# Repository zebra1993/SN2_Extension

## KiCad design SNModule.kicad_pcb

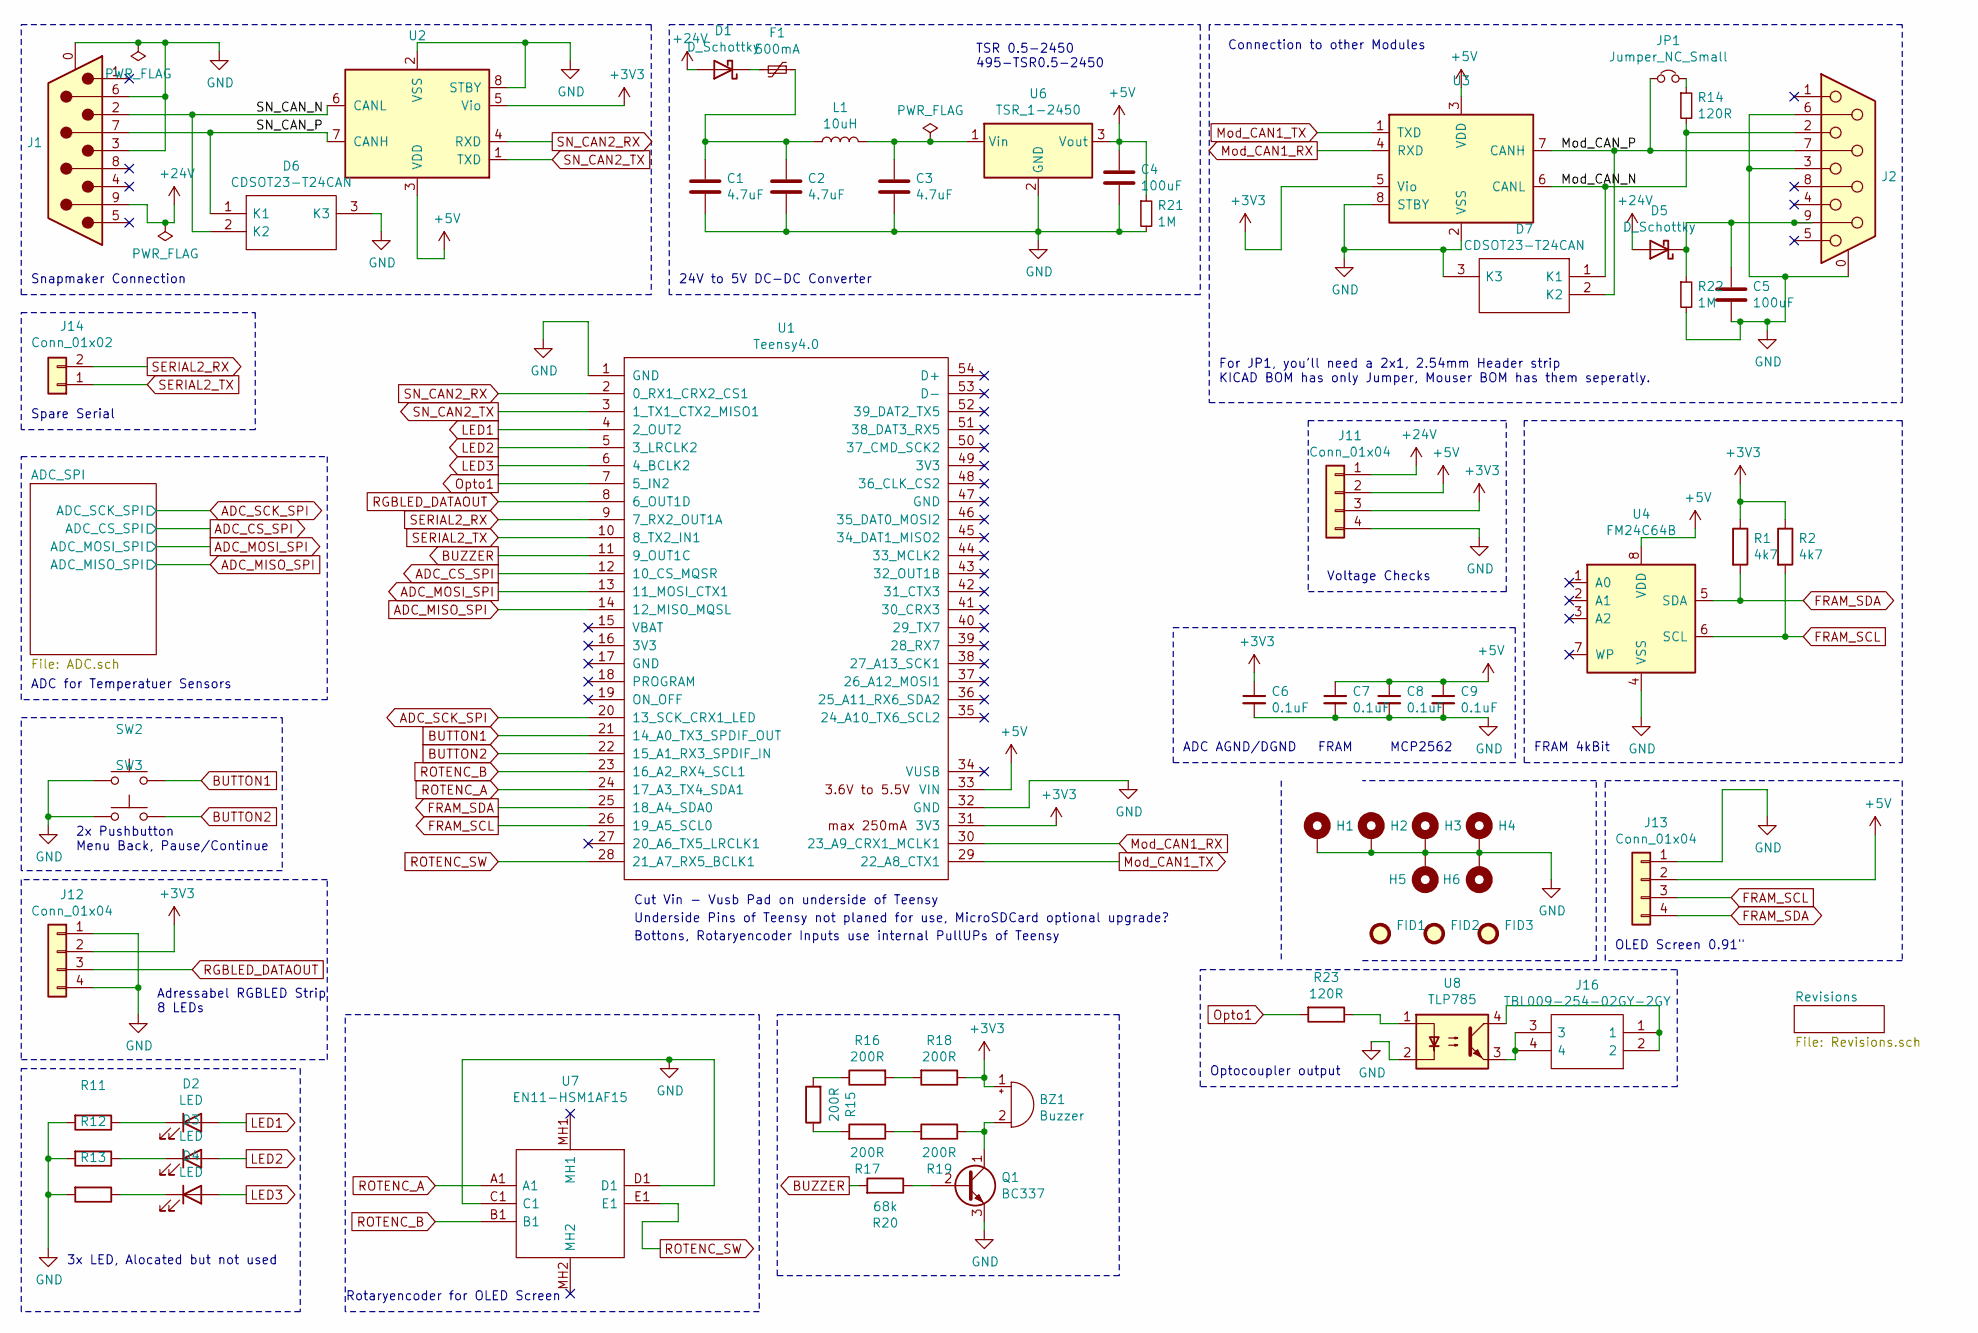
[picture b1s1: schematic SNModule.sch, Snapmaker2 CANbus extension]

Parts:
BZ1: Buzzer; Buzzer_TDK_12.2x6.5RM5; Manufacturer_Part_Number PS1240P02BT; Mouser Part Number 810-PS1240P02BT
C1, C2, C3: 4.7uF; C_1206_HandSoldering; Manufacturer_Part_Number C1206C475K5PACTU; Mouser Part Number 80-C1206C475K5P
C4, C5: 100uF; CP_Elec_6.3x7.7; Manufacturer_Part_Number EEE-FTH101XAL; Mouser Part Number 667-EEE-FTH101XAL
C6, C7, C8, C9: 0.1uF; C_1206_HandSoldering; Manufacturer_Part_Number VJ1206Y104KXXAC; Mouser Part Number 77-VJ1206Y104KXXAC
D1: D_Schottky; D_1206; Manufacturer_Part_Number SD1206T040S1R0; Mouser Part Number 581-SD1206T040S1R0
D2, D3, D4: LED; LED_D5.0mm_FlatTop; Manufacturer_Part_Number LTL-307GE; Mouser Part Number 859-LTL-307GE
D5: D_Schottky; D_2114; Manufacturer_Part_Number SD2114S040S8R0; Mouser Part Number 581-SD2114S040S8R0
D6, D7: CDSOT23-T24CAN; SOT-23; Mouser Part Number 652-CDSOT23-T24CAN
F1: 500mA; Fuse_SMD1206_HandSoldering; Manufacturer_Part_Number 0ZCJ0025AF2E; Mouser Part Number 530-0ZCJ0025AF2E
FID1, FID2, FID3: Fiducial; Fiducial_0.5mm_Dia_1mm_Outer
H1, H2, H3, H4, H5, H6: MountingHole_Pad; MountingHole_4.3mm_M4_Pad_Via
J1: DB9_Male_MountingHoles; D09P23A4GV00LF; Manufacturer_Part_Number D09P23A4GV00LF; Mouser Part Number 649-D09P23A4GV00LF
J2: DB9_Female_MountingHoles; D09S23A4GV00LF; Manufacturer_Part_Number D09S23A4GV00LF; Mouser Part Number 649-D09S23A4GV00LF
J11, J12, J13: Conn_01x04; Socket_Strip_Straight_1x04_Pitch2.54mm; Manufacturer_Part_Number SLW-104-01-T-S; Mouser Part Number 200-SLW10401TS
J14: Conn_01x02; Pin_Header_Straight_1x02_Pitch2.54mm; Manufacturer_Part_Number SLW-102-01-T-S; Mouser Part Number 200-SLW10201TS
J16: TBL009-254-02GY-2GY; TBL00925402GY2GY; Mouser Part Number 490-TBL00925402GY2GY
JP1: Jumper_NC_Small; Pin_Header_Straight_1x02_Pitch2.54mm; Manufacturer_Part_Number SX1100-B; Mouser Part Number 806-SX1100-B
L1: 10uH; L_TracoPower_TCK-047_5.2x5.8mm; Manufacturer_Part_Number TCK-047; Mouser Part Number 495-TCK-047
Q1: BC337; TO-92_Inline_Wide; Manufacturer_Part_Number BC33716TFR; Mouser Part Number 512-BC33716TFR
R1, R2: 4k7; R_1206_HandSoldering; Manufacturer_Part_Number CRCW12064K70FKEA; Mouser Part Number 71-CRCW1206-4.7K-E3
R11, R12, R13, R15, R16, R17, R18, R19: 200R; R_1206_HandSoldering; Manufacturer_Part_Number CRCW1206200RFKEA; Mouser Part Number 71-CRCW1206-200-E3
R14, R23: 120R; R_1206_HandSoldering; Manufacturer_Part_Number CRCW1206120RFKEAC; Mouser Part Number 71-CRCW1206120RFKEAC
R20: 68k; R_1206_HandSoldering; Manufacturer_Part_Number CRCW120668K0FKEA; Mouser Part Number 71-CRCW1206-68K-E3
R21, R22: 1M; R_1206_HandSoldering; Manufacturer_Part_Number CRCW12061M00FKEAC; Mouser Part Number 71-CRCW12061M00FKEAC
SW2, SW3: SW_Push; SW_PUSH_6mm_h4.3mm; Manufacturer_Part_Number ADTS61KV; Mouser Part Number 642-ADTS61KV
U1: Teensy4.0; Teensy40_THT; Manufacturer_Part_Number 4323; Mouser Part Number 485-4323
U2, U3: MCP2562-E-P; DIP-8_W7.62mm_Socket; Manufacturer_Part_Number MCP2562-E/P; Mouser Part Number 579-MCP2562-E/P
U4: FM24C64B; SOIC-8_3.9x4.9mm_Pitch1.27mm; Manufacturer_Part_Number FM24C64B-G; Mouser Part Number 877-FM24C64B-G
U6: TSR_1-2450; DCDC-Conv_TRACO_TSR-1; Manufacturer_Part_Number TSR0.5-2450; Mouser Part Number 495-TSR0.5-2450
U7: EN11-HSM1AF15; EN11HSM1AF15; Mouser Part Number 858-EN11-HSM1AF15
U8: TLP785; DIP-4_W7.62mm_LongPads; Manufacturer_Part_Number TLP785(D4-GR,F; Mouser Part Number 757-TLP785D4-GRF

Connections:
+3V3: BZ1.1 (-), C6.1, J11.3, J12.2, R1.1, R2.1, R18.1, U1.31 (3V3), U2.5 (Vio), U3.5 (Vio); also elsewhere on the board
+5V: C4.1, C7.1, C8.1, C9.1, J11.2, J13.2, R21.1, U1.33 (VIN), U2.3 (VDD), U3.3 (VDD), U4.8 (VDD), U6.3 (Vout)
+24V: D1.2 (A), D5.2 (A), J1.9, J11.1
/Mod_CAN_N: D7.1 (K1), J2.2, R14.2, U3.6 (CANL)
/Mod_CAN_P: D7.2 (K2), J2.7, JP1.1, U3.7 (CANH)
/SN_CAN_N: D6.2 (K2), J1.2, U2.6 (CANL)
/SN_CAN_P: D6.1 (K1), J1.7, U2.7 (CANH)
ADC_CS_SPI: U1.12 (10_CS_MQSR); also elsewhere on the board
ADC_MISO_SPI: U1.14 (12_MISO_MQSL); also elsewhere on the board
ADC_MOSI_SPI: U1.13 (11_MOSI_CTX1); also elsewhere on the board
ADC_SCK_SPI: U1.20 (13_SCK_CRX1_LED); also elsewhere on the board
BUTTON1: SW2.2, U1.21 (14_A0_TX3_SPDIF_OUT)
BUTTON2: SW3.2, U1.22 (15_A1_RX3_SPDIF_IN)
BUZZER: R20.2, U1.11 (9_OUT1C)
FRAM_SCL: J13.3, R2.2, U1.26 (19_A5_SCL0), U4.6 (SCL)
FRAM_SDA: J13.4, R1.2, U1.25 (18_A4_SDA0), U4.5 (SDA)
GND: C1.2, C2.2, C3.2, C4.2, C5.2, C6.2, C7.2, C8.2, C9.2, D6.3 (K3), D7.3 (K3), H1.1, H2.1, H3.1, H4.1, H5.1, H6.1, J1.0 (PAD), J1.3, J1.6, J2.0 (PAD), J2.3, J2.6, J11.4, J12.1, J12.4, J13.1, Q1.3 (E), R11.2, R12.2, R13.2, R21.2, R22.2, SW2.1, SW3.1, U1.1 (GND), U1.32 (GND), U2.2 (VSS), U2.8 (STBY), U3.2 (VSS), U3.8 (STBY), U4.4 (VSS), U6.2 (GND), U7.C1, U7.D1, U8.2; also elsewhere on the board
LED1: D2.2 (A), U1.4 (2_OUT2)
LED2: D3.2 (A), U1.5 (3_LRCLK2)
LED3: D4.2 (A), U1.6 (4_BCLK2)
Mod_CAN1_RX: U1.30 (23_A9_CRX1_MCLK1), U3.4 (RXD)
Mod_CAN1_TX: U1.29 (22_A8_CTX1), U3.1 (TXD)
unnamed: BZ1.2 (+), Q1.1 (C), R19.1
unnamed: C1.1, C2.1, F1.1, L1.1
unnamed: C3.1, L1.2, U6.1 (Vin)
unnamed: C5.1, D5.1 (K), J2.9, R22.1
unnamed: D1.1 (K), F1.2
unnamed: D2.1 (K), R11.1
unnamed: D3.1 (K), R12.1
unnamed: D4.1 (K), R13.1
unnamed: J16.1, J16.2, U8.4
unnamed: J16.3, J16.4, U8.3
unnamed: JP1.2, R14.1
unnamed: Q1.2 (B), R20.1
unnamed: R15.1, R17.2
unnamed: R15.2, R16.1
unnamed: R16.2, R18.2
unnamed: R17.1, R19.2
unnamed: R23.1, U8.1
Opto1: R23.2, U1.7 (5_IN2)
RGBLED_DATAOUT: J12.3, U1.8 (6_OUT1D)
ROTENC_A: U1.24 (17_A3_TX4_SDA1), U7.A1
ROTENC_B: U1.23 (16_A2_RX4_SCL1), U7.B1
ROTENC_SW: U1.28 (21_A7_RX5_BCLK1), U7.E1
SERIAL2_RX: J14.2, U1.9 (7_RX2_OUT1A)
SERIAL2_TX: J14.1, U1.10 (8_TX2_IN1)
SN_CAN2_RX: U1.2 (0_RX1_CRX2_CS1), U2.4 (RXD)
SN_CAN2_TX: U1.3 (1_TX1_CTX2_MISO1), U2.1 (TXD)

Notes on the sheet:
Cut Vin - Vusb Pad on underside of Teensy
Underside Pins of Teensy not planed for use, MicroSDCard optional upgrade?
24V to 5V DC-DC Converter
Snapmaker Connection
Adressabel RGBLED Strip 8 LEDs
ADC for Temperatuer Sensors
Spare Serial
Rotaryencoder for OLED Screen
2x Pushbutton Menu Back, Pause/Continue
Bottons, Rotaryencoder Inputs use internal PullUPs of Teensy
OLED Screen 0.91"
FRAM 4kBit
Voltage Checks
3x LED, Alocated but not used
MCP2562
FRAM
ADC AGND/DGND
For JP1, you'll need a 2x1, 2.54mm Header strip KICAD BOM has only Jumper, Mouser BOM has them seperatly.
Connection to other Modules
TSR 0.5-2450 495-TSR0.5-2450
Optocoupler output

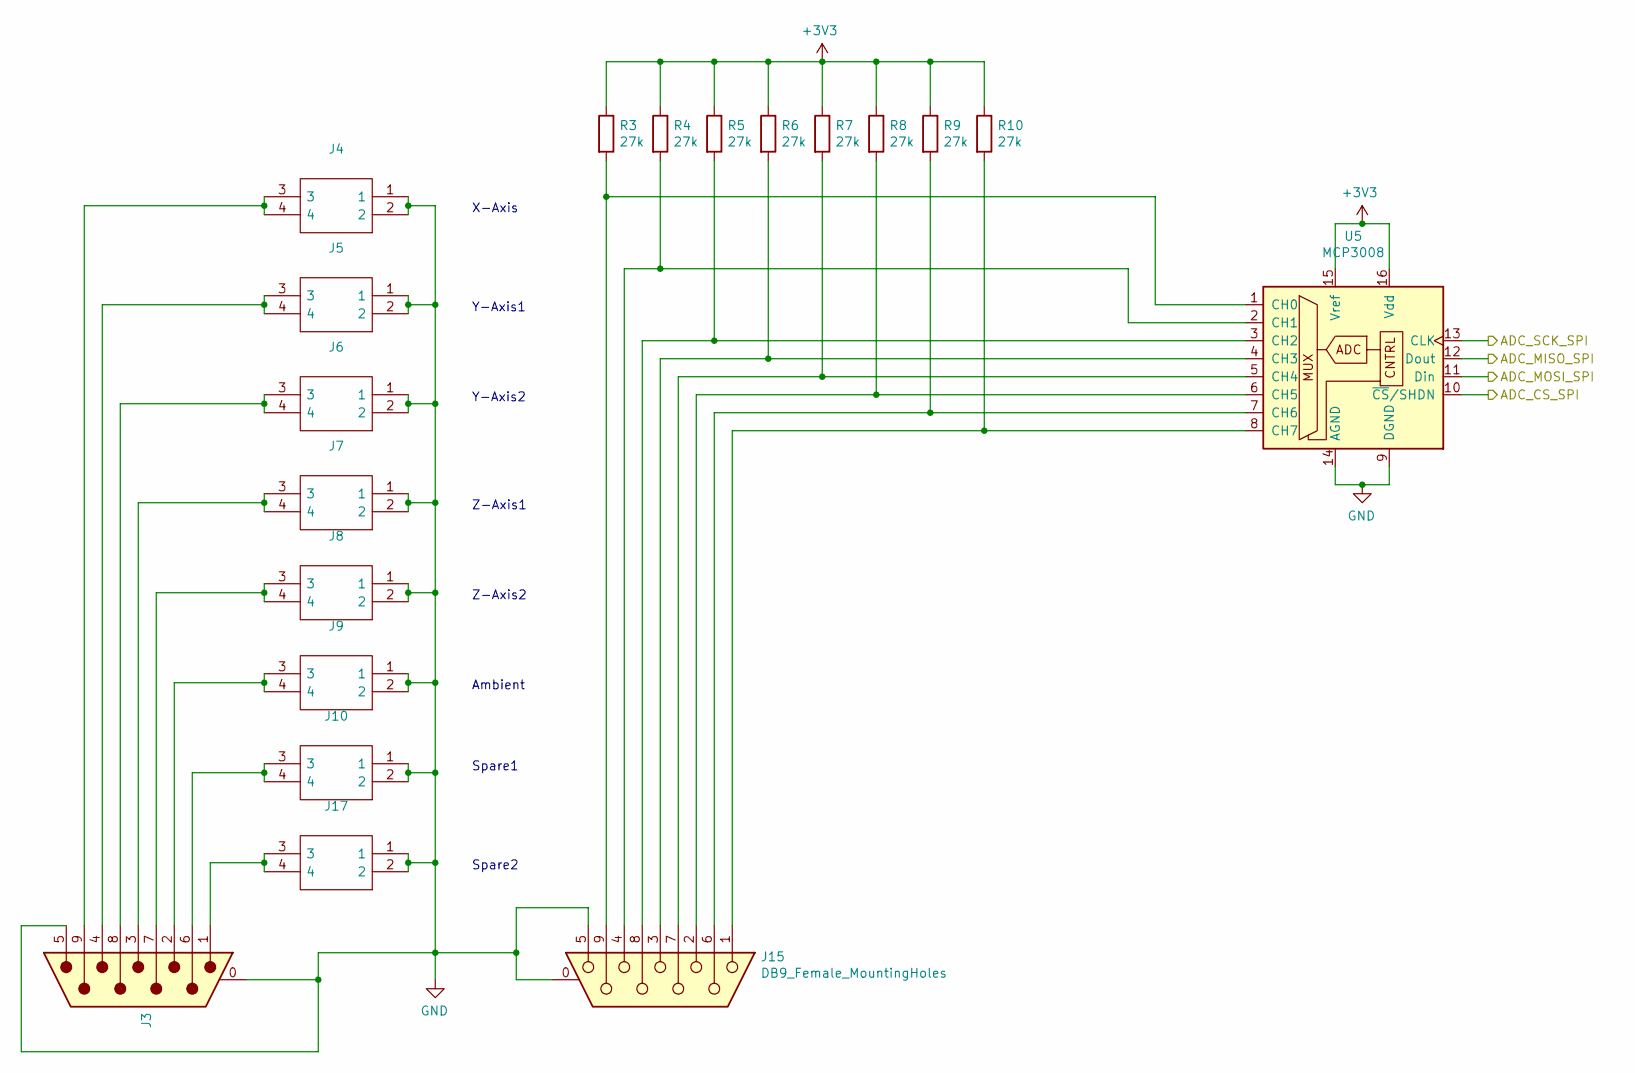
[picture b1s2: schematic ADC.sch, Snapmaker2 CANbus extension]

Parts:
J3: DB9_Male_MountingHoles; D09P23A4GV00LF; Manufacturer_Part_Number D09P23A4GV00LF; Mouser Part Number 649-D09P23A4GV00LF
J4, J5, J6, J7, J8, J9, J10, J17: TBL009-254-02GY-2GY; TBL00925402GY2GY; Mouser Part Number 490-TBL00925402GY2GY
J15: DB9_Female_MountingHoles; D09S23A4GV00LF; Mouser Part Number 649-D09S23A4GV00LF
R3, R4, R5, R6, R7, R8: 27k; R_1206_HandSoldering; Manufacturer_Part_Number CRCW120627K0FKEA; Mouser Part Number 71-CRCW1206-27K-E3
R9, R10: 27k; R_1206_HandSoldering; Mouser Part Number 71-CRCW1206-27K-E3
U5: MCP3008; DIP-16_W7.62mm_Socket; Manufacturer_Part_Number MCP3008-I/P; Mouser Part Number 579-MCP3008-I/P

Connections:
+3V3: R3.1, R4.1, R5.1, R6.1, R7.1, R8.1, R9.1, R10.1, U5.15 (Vref), U5.16 (Vdd); also elsewhere on the board
ADC_CS_SPI: U5.10 (~CS~/SHDN); also elsewhere on the board
ADC_MISO_SPI: U5.12 (Dout); also elsewhere on the board
ADC_MOSI_SPI: U5.11 (Din); also elsewhere on the board
ADC_SCK_SPI: U5.13 (CLK); also elsewhere on the board
GND: J3.0 (PAD), J3.5, J4.1, J4.2, J5.1, J5.2, J6.1, J6.2, J7.1, J7.2, J8.1, J8.2, J9.1, J9.2, J10.1, J10.2, J15.0 (PAD), J15.5, J17.1, J17.2, U5.9 (DGND), U5.14 (AGND); also elsewhere on the board
unnamed: J3.2, J9.3, J9.4
unnamed: J3.3, J7.3, J7.4
unnamed: J3.4, J5.3, J5.4
unnamed: J3.7, J8.3, J8.4
unnamed: J3.8, J6.3, J6.4
unnamed: J3.9, J4.3, J4.4
unnamed: J3.6, J10.3, J10.4
unnamed: J15.1, R10.2, U5.8 (CH7)
unnamed: J15.2, R8.2, U5.6 (CH5)
unnamed: J15.3, R6.2, U5.4 (CH3)
unnamed: J15.4, R4.2, U5.2 (CH1)
unnamed: J15.6, R9.2, U5.7 (CH6)
unnamed: J15.7, R7.2, U5.5 (CH4)
unnamed: J15.8, R5.2, U5.3 (CH2)
unnamed: J15.9, R3.2, U5.1 (CH0)
unnamed: J3.1, J17.3, J17.4

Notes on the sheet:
Spare1
Spare2
X-Axis
Y-Axis1
Y-Axis2
Z-Axis1
Z-Axis2
Ambient

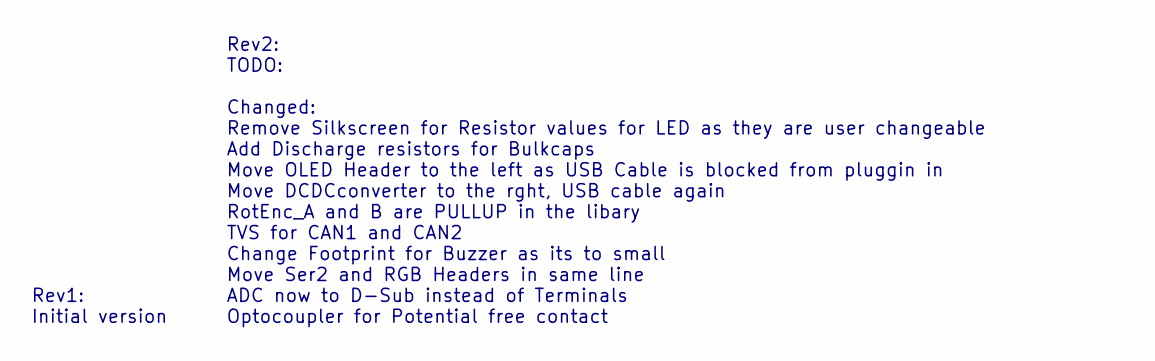
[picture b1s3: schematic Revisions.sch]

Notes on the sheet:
Rev1: Initial version
Rev2: TODO: Changed: Remove Silkscreen for Resistor values for LED as they are user changeable Add Discharge resistors for Bulkcaps Move OLED Header to the left as USB Cable is blocked from pluggin in Move DCDCconverter to the rght, USB cable again RotEnc_A and B are PULLUP in the libary TVS for CA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

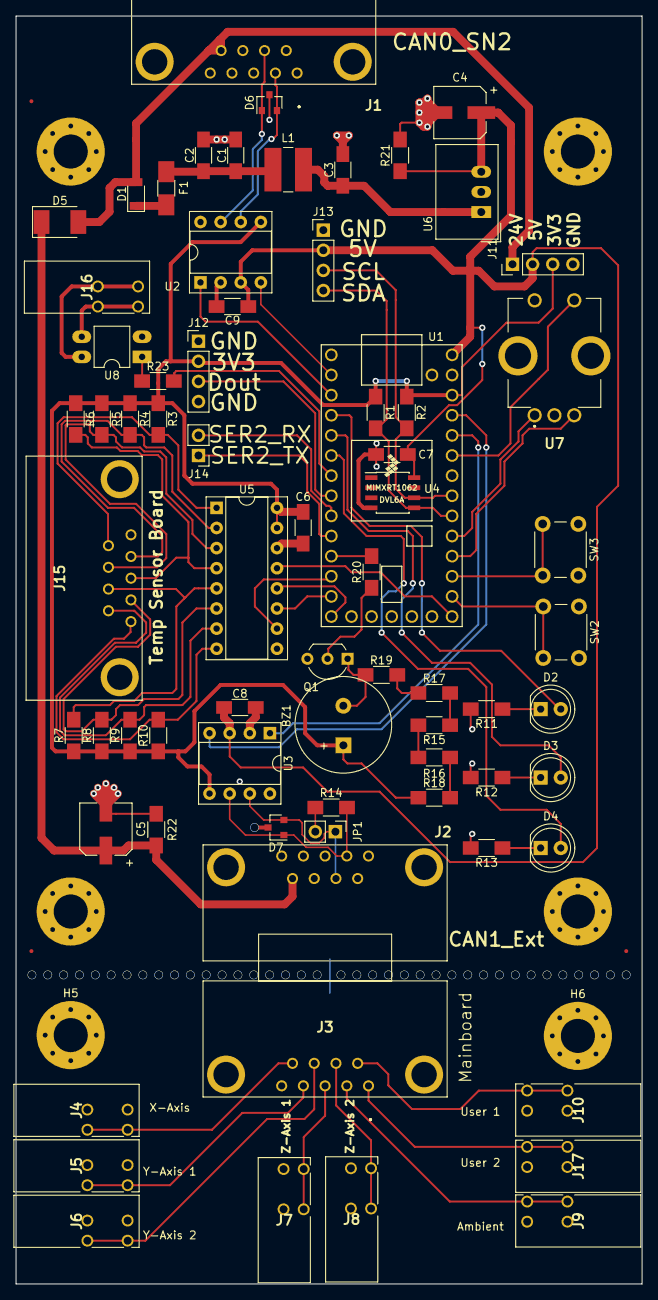
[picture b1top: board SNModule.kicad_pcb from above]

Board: 2 copper layers, 79.0 x 160.0 mm, 80 parts (0 on the bottom side), 64 nets.

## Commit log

2021-01-16 Initial Comit to Github, Rev1 of Board
2021-01-30 Rev1
    Orderd and ariving soon
2021-02-06 Rev1.1
    Mostly as Orderd, some small none function changes to Rev1
2021-04-09 Rev2 done
    Orderd and Assembeld PCB, works sofar, no magic Smoke sofar :D
2023-12-09 Last firmware of the Module
    Firmware is as is, OLED did work somewhat, Beeper worked. Canbus mostly? if you set the OLED screen to update to often, your CANbus will start to have issues.
    Check "../include/Designstuff.h" for some notes, code in geenral has a bunch of coments in it. its been ages since ive worked on it though.
    You'll need a modified controller version to allow to send custom packets to custom IDs.
    Unfortunatly i dont have that firmware anymore. (its vastly out of date anyway)
    Its basicly an additional M-Code that takes the arguments to be sent out. (Use what ever Number you want to use though)
    (M instead of G Code because its not Geometry but Misellaneous in its use
